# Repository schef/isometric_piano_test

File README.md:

# Isometric Piano — 60-Key Hall-Effect MIDI Controller

> **Latest pin-number decision:** OH49E-S uses EasyEDA convention
> **1 VCC / 2 VOUT / 3 GND**, consistently in the active symbol and footprint.
> Physical wiring unchanged; see [verification](OH49E_EASYEDA_NUMBERING.md).

> **Latest sensor approval (2026-11-04):** owner selected **OH49E-S / C85573**.
> Schematic migration and remapped footprint assignment are implemented; the PCB
> is not synchronized. See [migration and verification](OH49E_FOOTPRINT_MIGRATION.md)
> for remaining layout/tooling gates.
> No fabrication approval implied.

> **Current hardware decision (2026-11-04):** Gateron KS-20 White switches,
> existing 2.5 V ADC reference / Range 1, and Fluxpad V2 sensing geometry and
> PCB thickness. See [SWITCH_RANGE_DECISION.md](SWITCH_RANGE_DECISION.md).
> No KiCad change or fabrication approval has been made.

> **Sensor finding:** Fluxpad V2 assembly fields specify **OH49E-S / C85573**
> despite a DRV5056 symbol label. The owner has now selected OH49E-S for
> Keyboard12; its schematic now uses a native-pinout OH49E-S symbol.
> See [the investigation](FLUXPAD_SENSOR_IDENTIFICATION.md).

The main project is the **PCB design** for a modular, velocity-sensitive USB MIDI keyboard using
Hall-effect switches. The goal is **60 keys, built from five identical 12-key
sensor boards and one Raspberry Pi Pico 2 master carrier**.

The original three-key Fluxpad V2 experiment is preserved as
[example firmware](examples/fluxpad_midi/README.md), not the main controller.

## Main controller architecture

- **Keys:** Gateron KS-20 White magnetic switches with DSA-profile keycaps.
- **Sensing:** one OH49E-S / C85573 per key; schematic migrated, physical
  footprint assigned; PCB migration and assembly qualification pending.
- **Key boards:** 12 sensors and one ADS7953 SPI ADC per board; no local MCU.
- **Master:** Raspberry Pi Pico 2 on a carrier with USB-C and a dedicated
  3.3 V supply for the sensor boards.
- **Interconnect:** shared SPI clock/data, with a separate chip-select per board.
- **MIDI:** 60 chromatic notes, MIDI 36–95, over USB.
- **Dynamics:** measure travel time between two sensor thresholds and convert
  it to MIDI velocity, with per-key calibration planned.
- **Scan target:** 4 kHz per key, independent of USB logging/transmission.

See [PCB_DESIGN.md](PCB_DESIGN.md) for the detailed hardware specification,
component selections, and open design decisions. It is a design specification,
not a claim that the hardware or SPI implementation has been validated.

## Project status

**Start the hardware handover with [HANDOVER.md](HANDOVER.md).** The current KiCad
project is `ECAD/Keyboard12/Keyboard12/Keyboard12.kicad_pro`.

**Current next task:** restore Konnect's PCB Editor connection and review a
coordinated PCB net/geometry update using the remapped footprint. Resolve the
remaining keepout, assembly and physical-stackup checks through supported tools.
The thickness target remains 1.0 mm. The owner selected ADS7953 / REF5025, Range 1 (0–2.5 V);
prototype range margin, ADC settling and other electrical/mechanical checks remain
open (see [TODO.md](TODO.md) and [SWITCH_RANGE_DECISION.md](SWITCH_RANGE_DECISION.md)).
The saved DRV5056 design's full theoretical output exceeds this ADC range, but
actual switch clipping has not been measured. Fluxpad's measured OH49E-S response
does not qualify DRV5056A3. The system has **six boards
total: five populated 12-key sensor boards plus one Pico 2 master carrier**.
Only the five sensor ADCs need chip-select lines. There is no sixth-sensor-board
expansion requirement. See the handover for the 60-key throughput budget.

| Area | Status |
| --- | --- |
| 60-key architecture | Specified in `PCB_DESIGN.md` |
| Hardware design files | Existing work in `ECAD/`; not certified fabrication-ready |
| Pico 2 / ADS7953 controller firmware | Not implemented yet |
| Per-key calibration and flash persistence | Planned |
| Three-key Fluxpad example | Implemented; retained as a reference for sensing, velocity, and USB MIDI |

## Repository layout

```text
ECAD/                       Main controller hardware design work
PCB_DESIGN.md               60-key hardware and firmware specification
examples/fluxpad_midi/      Standalone three-key RP2040 reference firmware
  src/                     Key scanning, velocity curve, and TinyUSB support
  CMakeLists.txt           Pico SDK example build
  deploy.sh                Build and flash the Fluxpad example
CMakeLists.txt              Compatibility build entry point for the example
deploy.sh                   Compatibility deployment wrapper for the example
```

There is no main-controller firmware target yet. Root-level build/deploy commands
still operate on the **Fluxpad example only**, to preserve existing workflows.

## PCB development priorities

1. Validate the 12-key board and master carrier design, including Pico 2 SPI pin
   assignments, ADS7953 framing/sequencing, power, and connector wiring.
2. Establish the current schematic/layout completion state through an electrical
   and mechanical review; do not infer readiness from the design specification.
3. Resolve sensor/switch alignment, board dimensions, mounting, and inter-board connectors.
4. Run ERC/DRC and review component footprints, sourcing, and assembly constraints.
5. Prepare fabrication outputs only after review and approval. Firmware bring-up
   is a later validation step, not the current handover objective.

## Run the reference example

Install the official Raspberry Pi Pico SDK and ARM GCC toolchain, then:

```sh
export PICO_SDK_PATH=$HOME/git/pico-sdk
cmake -S examples/fluxpad_midi -B build/fluxpad_midi -DPICO_BOARD=pico
cmake --build build/fluxpad_midi
```

This produces `build/fluxpad_midi/fluxpad_midi.uf2` for **Fluxpad V2 / RP2040**,
not the Pico 2 master. See the [example README](examples/fluxpad_midi/README.md)
for flashing, serial monitoring, and the current velocity algorithm.

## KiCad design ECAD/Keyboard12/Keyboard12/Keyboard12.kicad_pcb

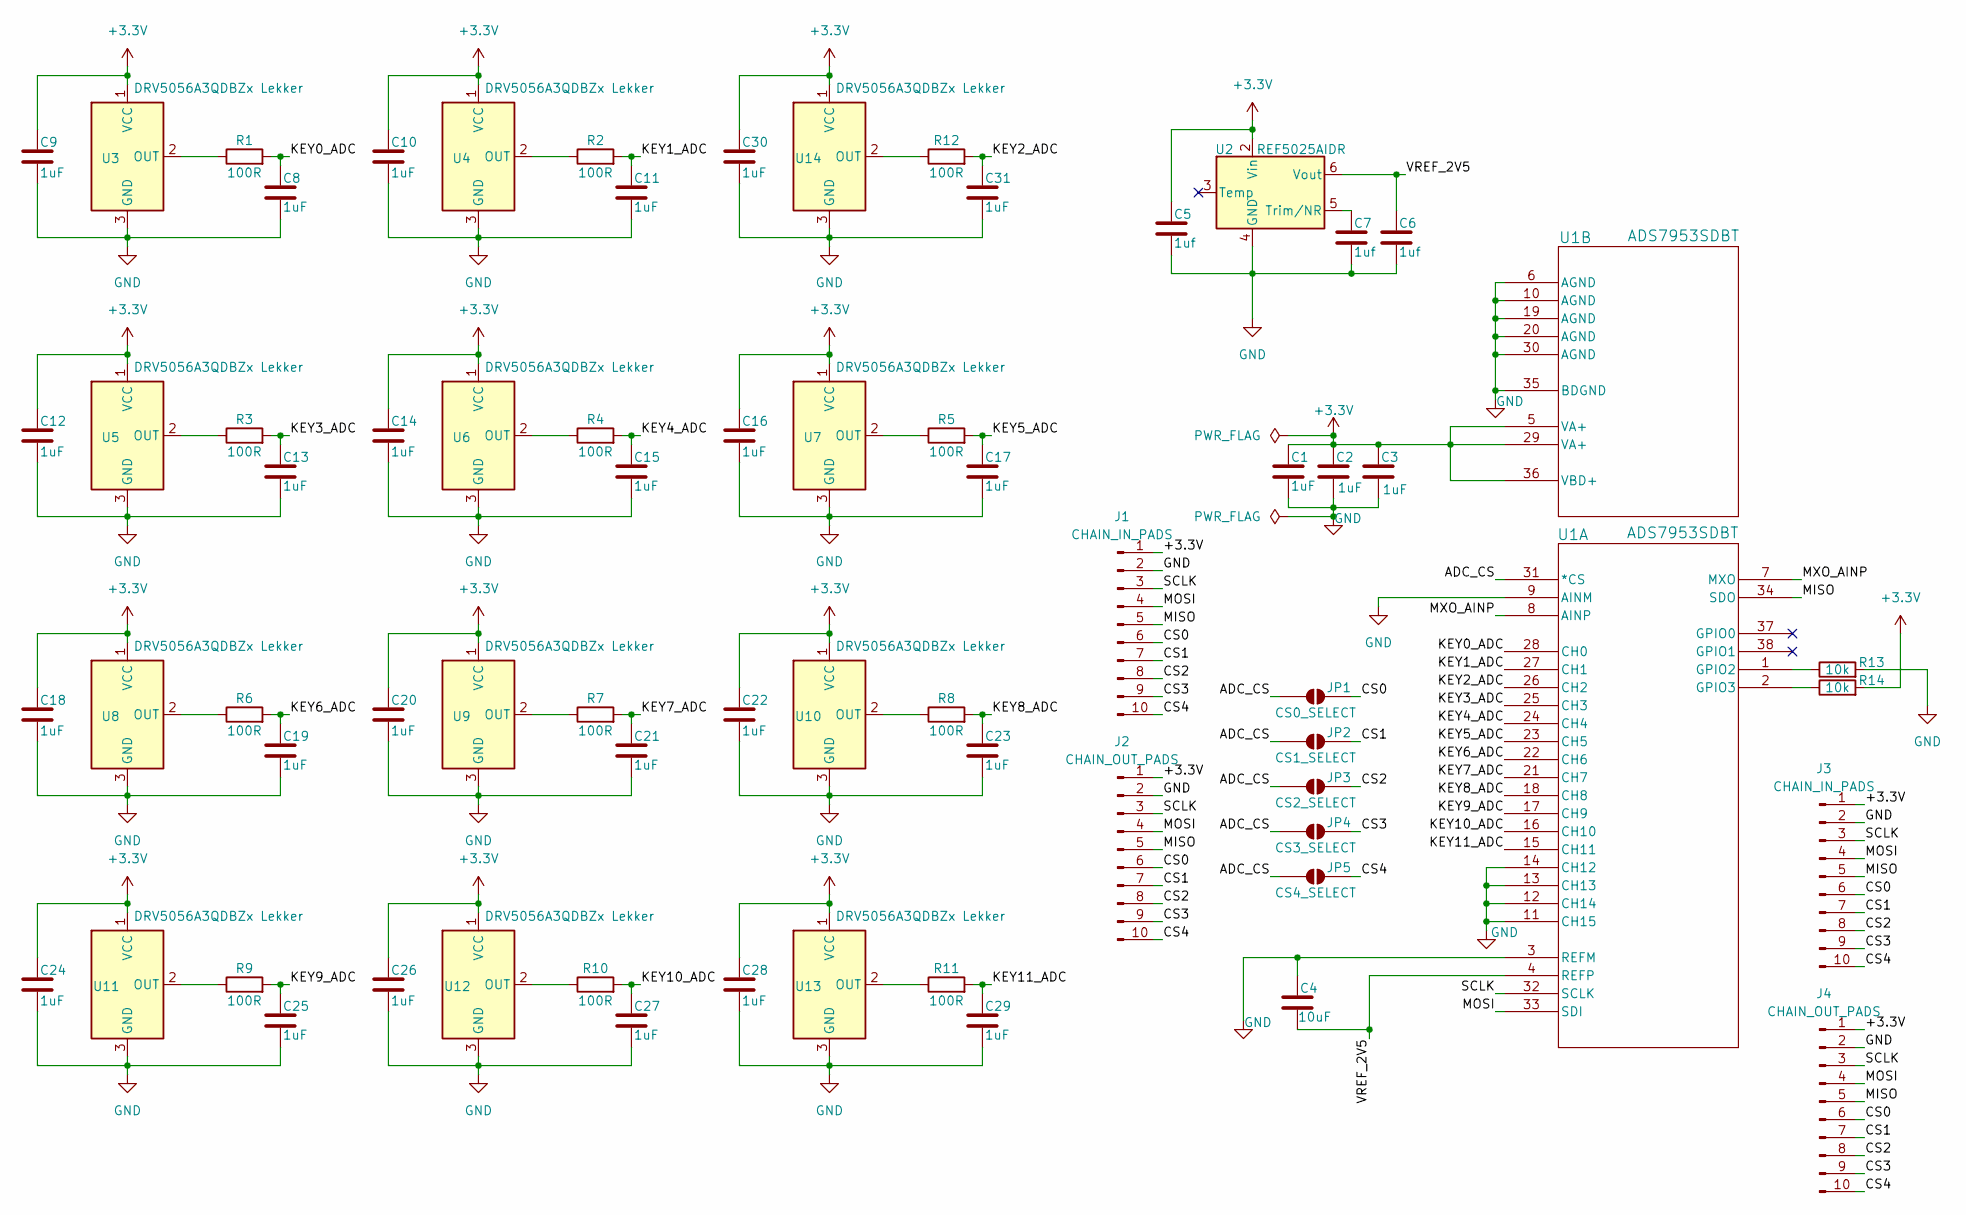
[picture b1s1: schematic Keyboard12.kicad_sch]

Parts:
C1, C2, C3, C8, C9, C10, C11, C12, C13, C14, C15, C16, C17, C18, C19, C20, C21, C22, C23, C24, C25, C26, C27, C28, C29, C30, C31: 1uF; C_0603_1608Metric_Pad1.08x0.95mm_HandSolder
C4: 10uF; C_0805_2012Metric_Pad1.18x1.45mm_HandSolder
C5, C6, C7: 1uf; C_0603_1608Metric_Pad1.08x0.95mm_HandSolder
J1: CHAIN_IN_PADS; Chain_1x10_SMD
J2: CHAIN_OUT_PADS; Chain_1x10_SMD
J3: CHAIN_IN_PADS; PinHeader_1x10_P2.54mm_Vertical
J4: CHAIN_OUT_PADS; PinHeader_1x10_P2.54mm_Vertical
JP1: CS0_SELECT; SolderJumper-2_P1.3mm_Open_Pad1.0x1.5mm
JP2: CS1_SELECT; SolderJumper-2_P1.3mm_Open_Pad1.0x1.5mm
JP3: CS2_SELECT; SolderJumper-2_P1.3mm_Open_Pad1.0x1.5mm
JP4: CS3_SELECT; SolderJumper-2_P1.3mm_Open_Pad1.0x1.5mm
JP5: CS4_SELECT; SolderJumper-2_P1.3mm_Open_Pad1.0x1.5mm
R1, R2, R3, R4, R5, R6, R7, R8, R9, R10, R11, R12: 100R; R_0603_1608Metric_Pad0.98x0.95mm_HandSolder
R13, R14: 10k; R_0603_1608Metric_Pad0.98x0.95mm_HandSolder
U1: ADS7953SDBT; DBT38; JLC Part C701092
U2: REF5025AIDR; SOIC-8_3.9x4.9mm_P1.27mm; JLC Part C11341
U3, U4, U5, U6, U7, U8, U9, U10, U11, U12, U13, U14: DRV5056A3QDBZx Lekker; SW_Cherry_MX_PCB_1.00u_hall_effect; JLC Part C85573

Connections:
+3.3V: C1.2, C2.2, C3.2, C5.1, C9.1, C10.1, C12.1, C14.1, C16.1, C18.1, C20.1, C22.1, C24.1, C26.1, C28.1, C30.1, J1.1, J2.1, J3.1, J4.1, R14.2, U1.5 (VA+), U1.29 (VA+), U1.36 (VBD+), U2.2 (Vin), U3.1 (VCC), U4.1 (VCC), U5.1 (VCC), U6.1 (VCC), U7.1 (VCC), U8.1 (VCC), U9.1 (VCC), U10.1 (VCC), U11.1 (VCC), U12.1 (VCC), U13.1 (VCC), U14.1 (VCC)
/ADC_CS: JP1.1 (A), JP2.1 (A), JP3.1 (A), JP4.1 (A), JP5.1 (A), U1.31 (*CS)
/CS0: J1.6, J2.6, J3.6, J4.6, JP1.2 (B)
/CS1: J1.7, J2.7, J3.7, J4.7, JP2.2 (B)
/CS2: J1.8, J2.8, J3.8, J4.8, JP3.2 (B)
/CS3: J1.9, J2.9, J3.9, J4.9, JP4.2 (B)
/CS4: J1.10, J2.10, J3.10, J4.10, JP5.2 (B)
/KEY0_ADC: C8.1, R1.2, U1.28 (CH0)
/KEY1_ADC: C11.1, R2.2, U1.27 (CH1)
/KEY2_ADC: C31.1, R12.2, U1.26 (CH2)
/KEY3_ADC: C13.1, R3.2, U1.25 (CH3)
/KEY4_ADC: C15.1, R4.2, U1.24 (CH4)
/KEY5_ADC: C17.1, R5.2, U1.23 (CH5)
/KEY6_ADC: C19.1, R6.2, U1.22 (CH6)
/KEY7_ADC: C21.1, R7.2, U1.21 (CH7)
/KEY8_ADC: C23.1, R8.2, U1.18 (CH8)
/KEY9_ADC: C25.1, R9.2, U1.17 (CH9)
/KEY10_ADC: C27.1, R10.2, U1.16 (CH10)
/KEY11_ADC: C29.1, R11.2, U1.15 (CH11)
/MISO: J1.5, J2.5, J3.5, J4.5, U1.34 (SDO)
/MOSI: J1.4, J2.4, J3.4, J4.4, U1.33 (SDI)
/MXO_AINP: U1.7 (MXO), U1.8 (AINP)
/SCLK: J1.3, J2.3, J3.3, J4.3, U1.32 (SCLK)
/VREF_2V5: C4.1, C6.1, U1.4 (REFP), U2.6 (Vout)
GND: C1.1, C2.1, C3.1, C4.2, C5.2, C6.2, C7.2, C8.2, C9.2, C10.2, C11.2, C12.2, C13.2, C14.2, C15.2, C16.2, C17.2, C18.2, C19.2, C20.2, C21.2, C22.2, C23.2, C24.2, C25.2, C26.2, C27.2, C28.2, C29.2, C30.2, C31.2, J1.2, J2.2, J3.2, J4.2, R13.2, U1.3 (REFM), U1.6 (AGND), U1.9 (AINM), U1.10 (AGND), U1.11 (CH15), U1.12 (CH14), U1.13 (CH13), U1.14 (CH12), U1.19 (AGND), U1.20 (AGND), U1.30 (AGND), U1.35 (BDGND), U2.4 (GND), U3.3 (GND), U4.3 (GND), U5.3 (GND), U6.3 (GND), U7.3 (GND), U8.3 (GND), U9.3 (GND), U10.3 (GND), U11.3 (GND), U12.3 (GND), U13.3 (GND), U14.3 (GND)
unnamed: R13.1, U1.1 (GPIO2)
unnamed: R14.1, U1.2 (GPIO3)
unnamed: C7.1, U2.5 (Trim/NR)
unnamed: R1.1, U3.2 (OUT)
unnamed: R2.1, U4.2 (OUT)
unnamed: R3.1, U5.2 (OUT)
unnamed: R4.1, U6.2 (OUT)
unnamed: R5.1, U7.2 (OUT)
unnamed: R6.1, U8.2 (OUT)
unnamed: R7.1, U9.2 (OUT)
unnamed: R8.1, U10.2 (OUT)
unnamed: R9.1, U11.2 (OUT)
unnamed: R10.1, U12.2 (OUT)
unnamed: R11.1, U13.2 (OUT)
unnamed: R12.1, U14.2 (OUT)

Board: 4 copper layers, 68 parts (68 on the bottom side), 40 nets, no tracks yet.
